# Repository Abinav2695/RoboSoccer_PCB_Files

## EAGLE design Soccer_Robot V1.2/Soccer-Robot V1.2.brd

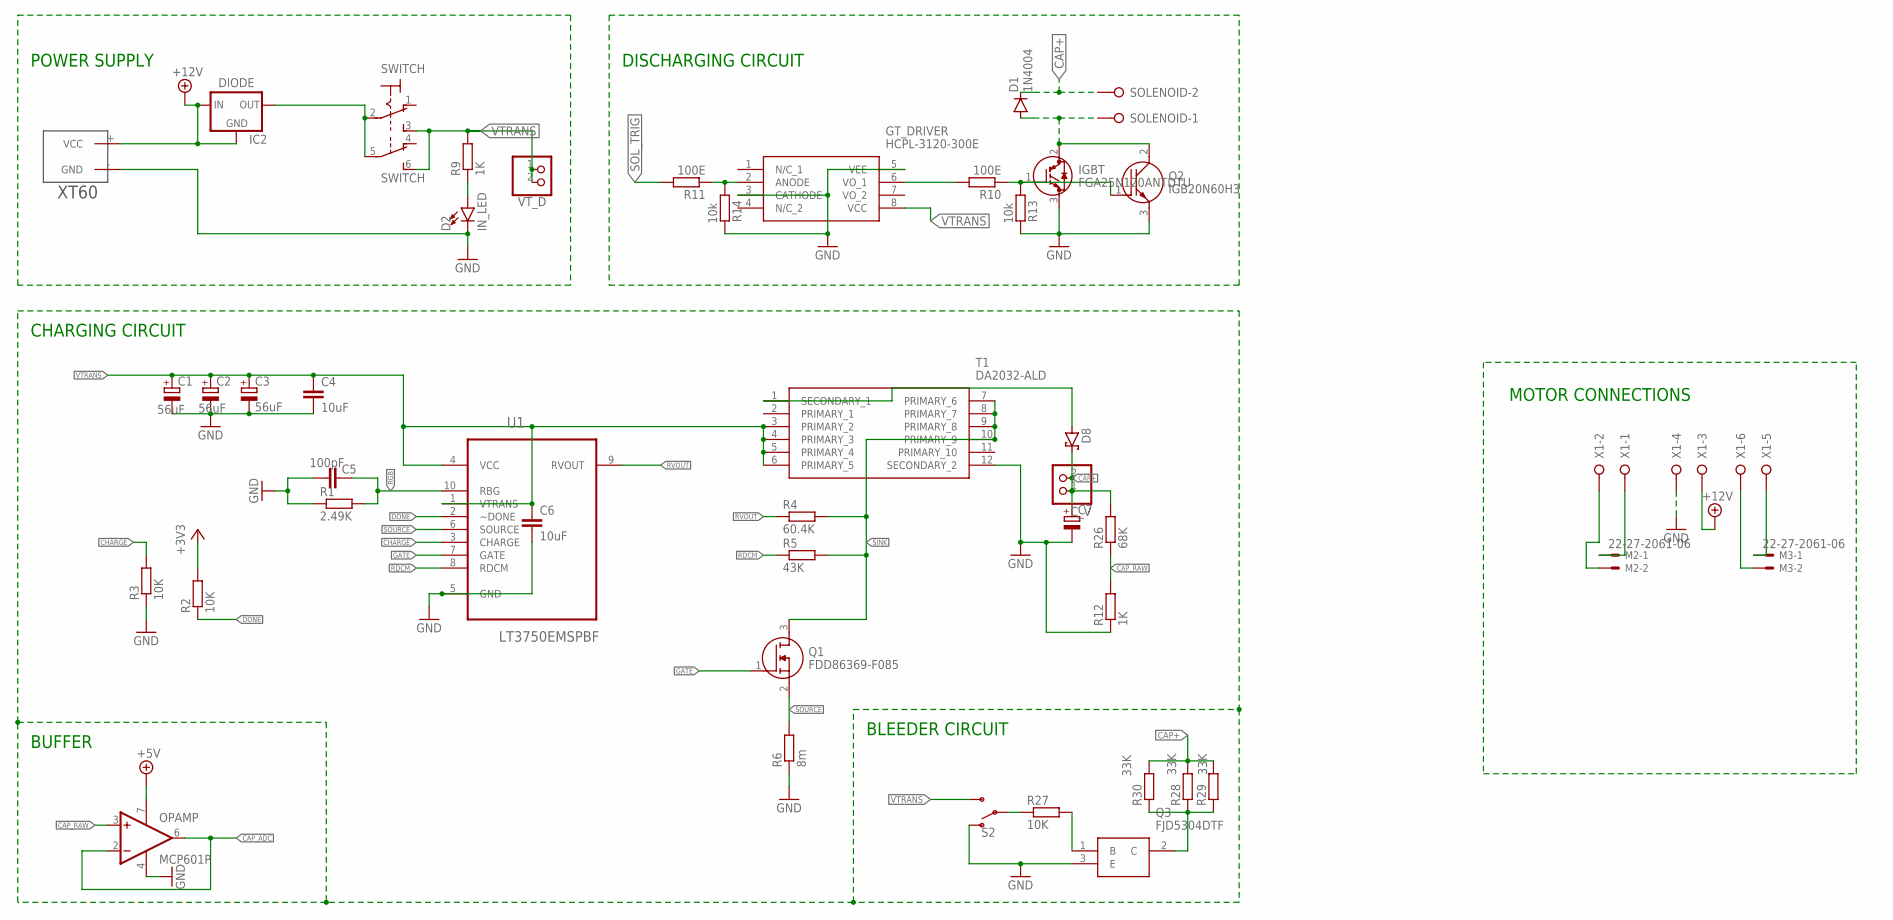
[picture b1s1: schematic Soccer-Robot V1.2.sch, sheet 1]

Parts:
C1, C2, C3: 56uF; E2,5-5
C4, C6: 10uF; C1206
C5: 100pF; C1206
C7: CPOL-EUE10-30; EB30D
C_V: PINHD-1X2; 1X02
D1: 1N4004; DO41-10
D2: IN_LED; LED_5MM
D8: SCHOTTKY-DIODESMC; SMC
GT_DRIVER: HCPL-3120-300E; HCPL-3120-GULL-WING
IC2: DIODE; TO252
IGBT: FGA25N120ANTDTU; TO545P500X1560X2420-3P
M2, M3: 22-27-2061-06; 6410-06
OPAMP: MCP601P; DIL08
Q1: FDD86369-F085; DPAK3-CASE-369AS
Q2: IGB20N60H3; IDB30E60
Q3: FJD5304DTF
R1: 2.49K; M1206
R2, R3, R27: 10K; M1206
R4: 60.4K; M1206
R5: 43K; M1206
R6: 8m; M1206
R9, R12: 1K; M1206
R10, R11: 100E; M1206
R13, R14: 10k; M1206
R26: 68K; M1206
R28, R29, R30: 33K; M1206
S2: SWITCH-SPDT-PTH-11.6X4.0MM; SWITCH_SPDT_PTH_11.6X4.0MM
SOLENOID: W237-02P; W237-132
SWITCH: 320-938
T1: DA2032-ALD; SOP250P2197X889-12N
U1: LT3750EMSPBF; SOP50P490X110-10N
U$1: XT60
VT_D: PINHD-1X2; 1X02
X1: W237-06P; W237-6P

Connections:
+3V3: R2.2; also elsewhere on the board
+5V: OPAMP.7 (V+); also elsewhere on the board
+12V: IC2.1 (GND), IC2.2 (IN), U$1.+ (VCC), X1.3; also elsewhere on the board
CAP+: C7.+, C_V.1, C_V.2, D1.C, D8.C, R26.2, R28.2, R29.2, R30.2, SOLENOID.2
CAP_ADC: OPAMP.2 (-IN), OPAMP.6 (OUT); also elsewhere on the board
CAP_RAW: OPAMP.3 (+IN), R12.2, R26.1
CHARGE: R3.2, U1.3 (CHARGE); also elsewhere on the board
DONE: R2.1, U1.2 (~DONE); also elsewhere on the board
GATE: Q1.1 (G), U1.7 (GATE)
GND: C1.-, C2.-, C3.-, C4.2, C5.2, C6.2, C7.-, D2.K (C), GT_DRIVER.3 (CATHODE), GT_DRIVER.5 (VEE), IGBT.3 (E), OPAMP.4 (V-), Q2.3 (E), Q3.3 (E), R1.1, R3.1, R6.1, R12.1, R13.2, R14.2, S2.1 (O), T1.12 (SECONDARY_2), U1.5 (GND), U$1.- (GND), X1.4; also elsewhere on the board
unnamed: R27.1, S2.2
unnamed: Q3.1 (B), R27.2
unnamed: D8.A, T1.1 (SECONDARY_1)
unnamed: D2.A, R9.1
unnamed: IGBT.1 (G), Q2.1 (G), R10.1, R13.1
unnamed: GT_DRIVER.6 (VO_1), R10.2
unnamed: D1.A, IGBT.2 (C), Q2.2 (C), SOLENOID.1
unnamed: GT_DRIVER.2 (ANODE), R11.1, R14.1
unnamed: M3.1, X1.5
unnamed: M3.2, X1.6
unnamed: M2.2, X1.2
unnamed: M2.1, X1.1
unnamed: Q3.2 (C), R28.1, R29.1, R30.1
RDCM: R5.1, U1.8 (RDCM)
RGB: C5.1, R1.2, U1.10 (RBG)
RVOUT: R4.1, U1.9 (RVOUT)
SINK: Q1.3 (D), R4.2, R5.2, T1.7 (PRIMARY_6), T1.8 (PRIMARY_7), T1.9 (PRIMARY_8), T1.10 (PRIMARY_9)
SOL_TRIG: R11.2; also elsewhere on the board
SOURCE: Q1.2 (S), R6.2, U1.6 (SOURCE)
VIN: IC2.3 (OUT), SWITCH.2, SWITCH.5
VTRANS: C1.+, C2.+, C3.+, C4.1, C6.1, GT_DRIVER.8 (VCC), R9.2, S2.3 (S), SWITCH.3 (S), SWITCH.6 (S), T1.3 (PRIMARY_2), T1.4 (PRIMARY_3), T1.5 (PRIMARY_4), T1.6 (PRIMARY_5), U1.1 (VTRANS), U1.4 (VCC), VT_D.1, VT_D.2

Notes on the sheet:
CHARGING CIRCUIT
BUFFER
POWER SUPPLY
DISCHARGING CIRCUIT
MOTOR CONNECTIONS
BLEEDER CIRCUIT

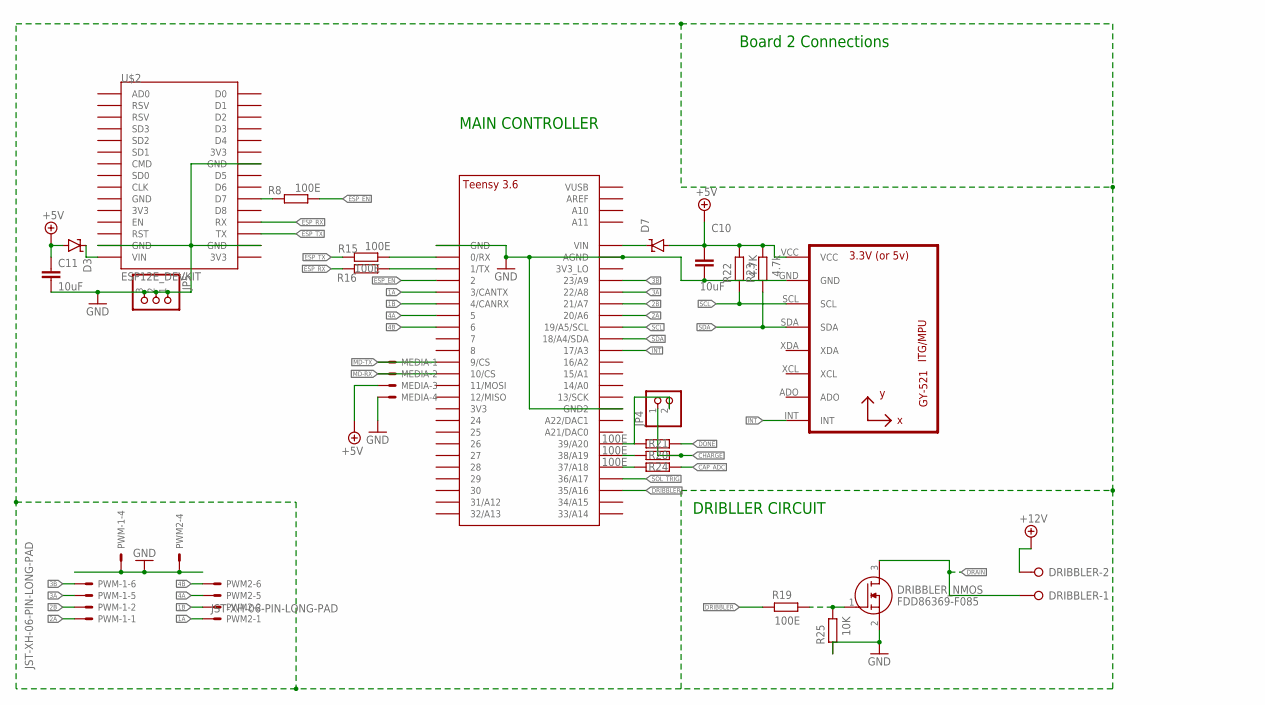
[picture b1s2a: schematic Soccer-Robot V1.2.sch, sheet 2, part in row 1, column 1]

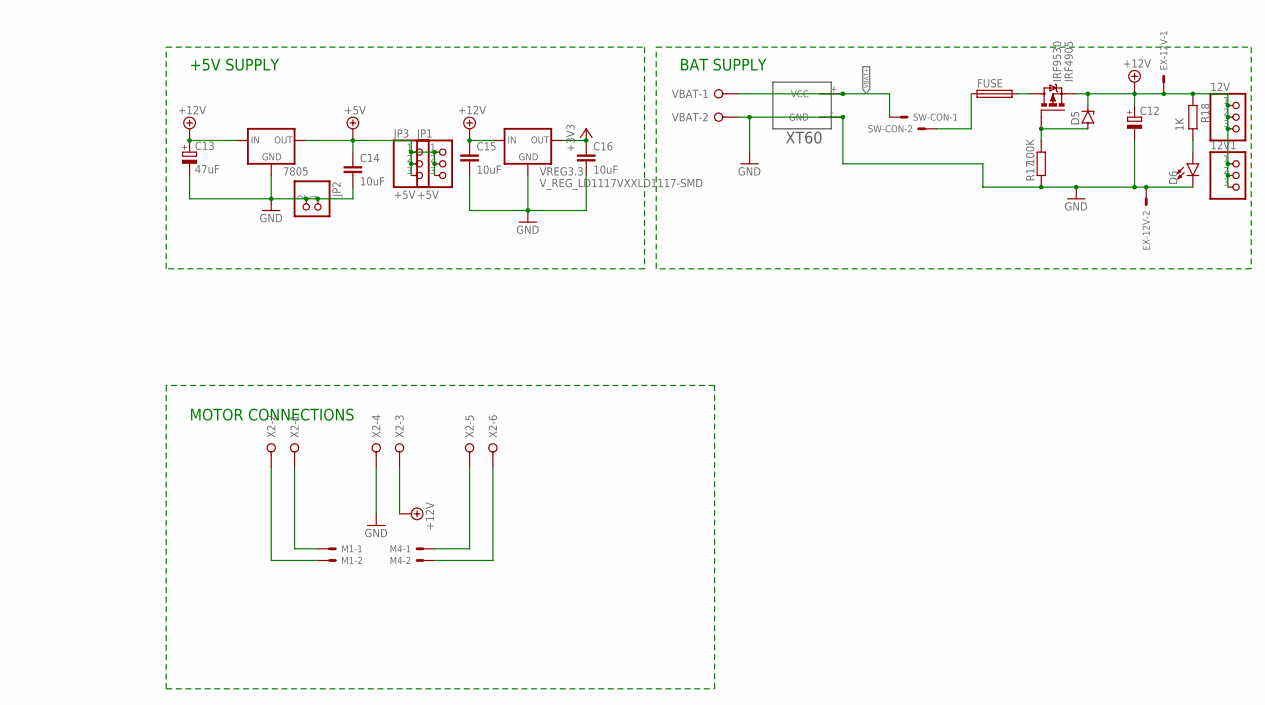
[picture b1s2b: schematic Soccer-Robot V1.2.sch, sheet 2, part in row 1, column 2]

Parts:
12V, 12V1: PINHD-1X3; 1X03
7805: 78XXS
C10, C11, C14, C15, C16: 10uF; C1206
C12: CPOL-EUE2.5-7; E2,5-7
C13: 47uF; E2,5-7
D3, D7: SUPPRESSOR-SMBG; SMBG
D5: ZENER-DIODEDO41Z10; DO41Z10
D6: LED5MM; LED_5MM
DRIBBLER: W237-02P; W237-132
DRIBBLER_NMOS: FDD86369-F085; DPAK3-CASE-369AS
EX-12V: KK-156-2
FUSE: SH22,5A
IRF4905: IRF9530; TO220BV
JP1, JP3: +5V; 1X03
JP2, JP4: PINHD-1X2; 1X02
JP5: PINHD-1X3; 1X03
M1, M4: 22-27-2061-06; 6410-06
MEDIA: JST-XH-04-PIN-LONG-PAD; JST-XH-04-PACKAGE-LONG-PAD
PWM2: JST-XH-06-PIN-LONG-PAD; JST-XH-06-PACKAGE-LONG-PAD
PWM-1: JST-XH-06-PIN-LONG-PAD; JST-XH-06-PACKAGE-LONG-PAD
R8, R15, R16, R19, R20, R21, R24: 100E; M1206
R17: 100K; M1206
R18: 1K; M1206
R22: 4.7K; M1206
R23: 4.7k; M1206
R25: 10K; M1206
SW-CON: KK-156-2
U2: GY-521MPU6050; GY-521
U$2: ESP12E_DEVKIT
U$3: TEENSY_3.5/3.6_BASIC
VBAT: W237-02P; W237-132
VBAT2: XT60
VREG3.3: V_REG_LD1117VXXLD1117-SMD; SOT223
X2: W237-06P; W237-6P

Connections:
1A: PWM2.1, U$3.3/CANTX
1B: PWM2.2, U$3.4/CANRX
2A: PWM-1.1, U$3.20/A6
2B: PWM-1.2, U$3.21/A7
3A: PWM-1.5, U$3.22/A8
3B: PWM-1.6, U$3.23/A9
4A: PWM2.5, U$3.5
4B: PWM2.6, U$3.6
+3V3: C16.1, VREG3.3.2 (OUT), VREG3.3.4 (OUT); also elsewhere on the board
+5V: 7805.OUT, C10.1, C11.1, C14.1, D3.A, D7.A, JP1.1, JP1.2, JP1.3, JP3.1, JP3.2, JP3.3, MEDIA.3, R22.1, R23.1, U2.VCC; also elsewhere on the board
+12V: 12V.1, 12V.2, 12V.3, 12V1.1, 12V1.2, 12V1.3, 7805.IN, C12.+, C13.+, C15.1, D5.C, DRIBBLER.2, EX-12V.1, IRF4905.S, R18.2, VREG3.3.3 (IN), X2.3; also elsewhere on the board
CAP_ADC: R24.2; also elsewhere on the board
CHARGE: JP4.1, R20.2; also elsewhere on the board
DONE: R21.2; also elsewhere on the board
DRAIN: DRIBBLER.1, DRIBBLER_NMOS.3 (D)
DRIBBLER: R19.2, U$3.35/A16
ESP_EN: R8.2, U$3.2
ESP_RX: R16.1, U$2.RX
ESP_TX: R15.1, U$2.TX
GND: 7805.GND, C10.2, C11.2, C12.-, C13.-, C14.2, C15.2, C16.2, D6.K (C), DRIBBLER_NMOS.2 (S), EX-12V.2, JP2.1, JP2.2, JP5.1, JP5.2, JP5.3, MEDIA.4, PWM2.4, PWM-1.4, R17.1, R25.2, U2.GND, U$2.GND@1 (GND), U$2.GND@2 (GND), U$2.GND@3 (GND), U$3.AGND, U$3.GND, U$3.GND2, VBAT.2, VBAT2.- (GND), VREG3.3.1 (GND), X2.4; also elsewhere on the board
INT: U2.INT, U$3.17/A3
MD-RX: MEDIA.2, U$3.10/CS
MD-TX: MEDIA.1, U$3.9/CS
unnamed: R8.1, U$2.D7
unnamed: R15.2, U$3.0/RX
unnamed: R16.2, U$3.1/TX
unnamed: FUSE.2, IRF4905.D
unnamed: D5.A, IRF4905.G, R17.2
unnamed: D6.A, R18.1
unnamed: DRIBBLER_NMOS.1 (G), R19.1, R25.1
unnamed: M4.1, X2.5
unnamed: M4.2, X2.6
unnamed: M1.1, X2.1
unnamed: R20.1, U$3.38/A19
unnamed: JP4.2, R21.1, U$3.39/A20
unnamed: R24.1, U$3.37/A18
unnamed: D3.C, U$2.VIN
unnamed: M1.2, X2.2
unnamed: FUSE.1, SW-CON.2
unnamed: D7.C, U$3.VIN
SCL: R22.2, U2.SCL, U$3.19/A5/SCL
SDA: R23.2, U2.SDA, U$3.18/A4/SDA
SOL_TRIG: U$3.36/A17; also elsewhere on the board
VBAT+: SW-CON.1, VBAT.1, VBAT2.+ (VCC)

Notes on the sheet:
MAIN CONTROLLER
+5V SUPPLY
BAT SUPPLY
MOTOR CONNECTIONS
DRIBLLER CIRCUIT
Board 2 Connections

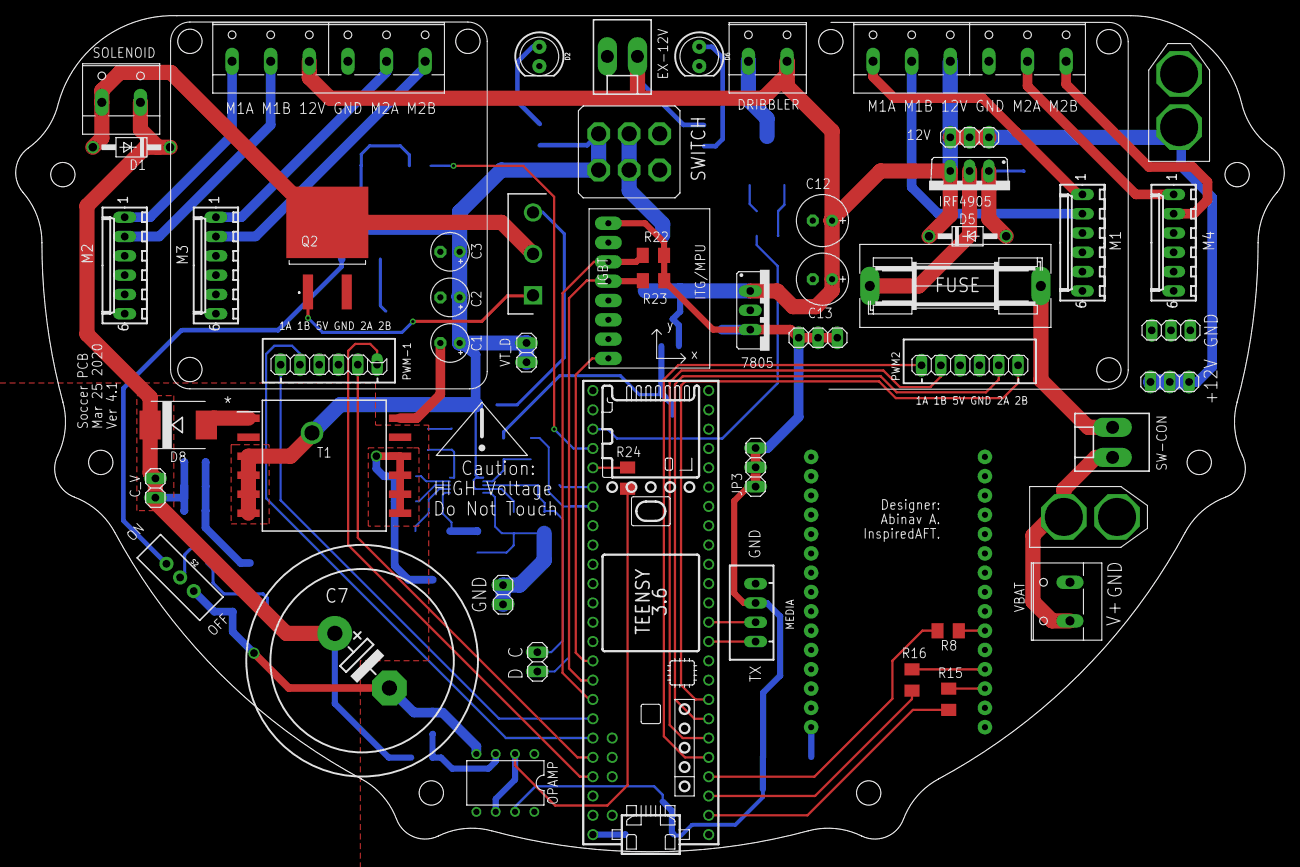
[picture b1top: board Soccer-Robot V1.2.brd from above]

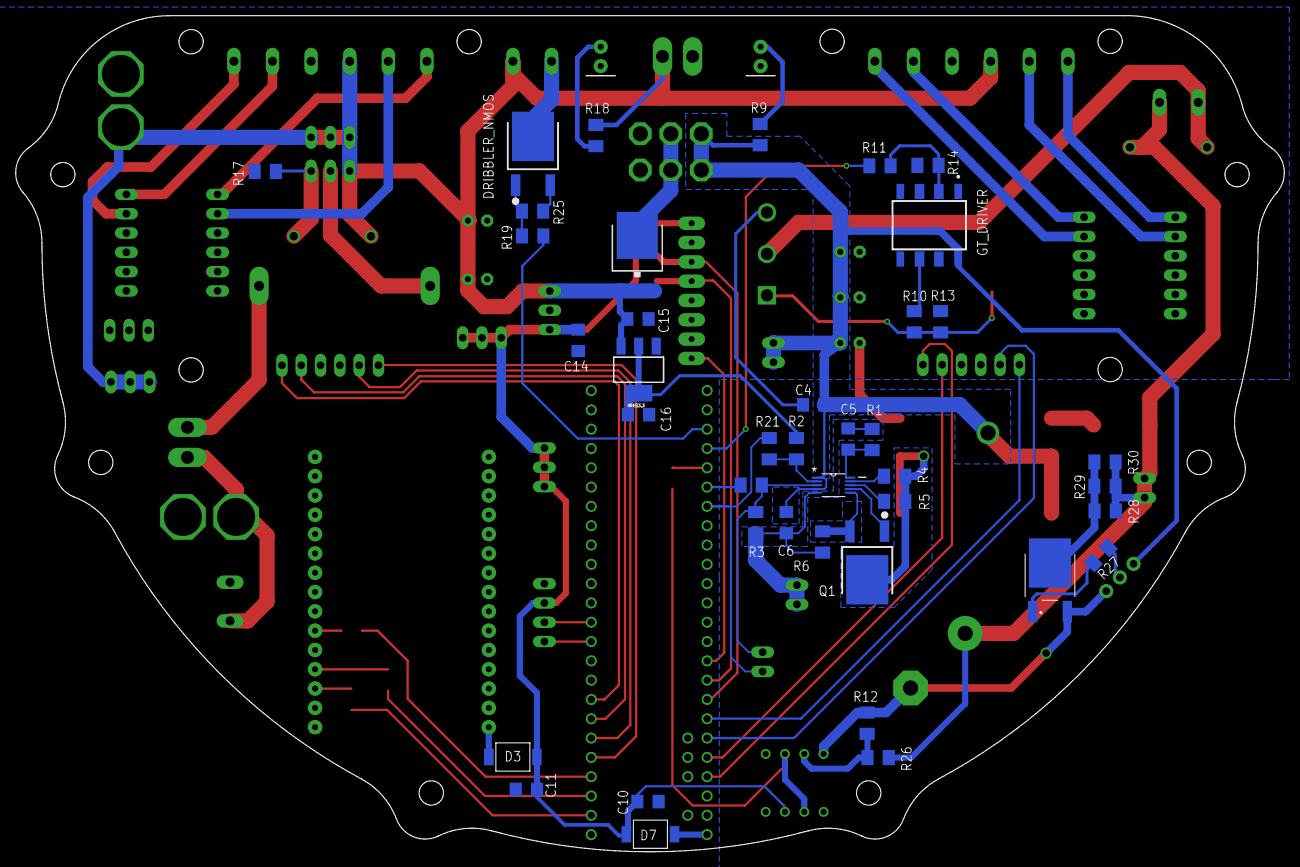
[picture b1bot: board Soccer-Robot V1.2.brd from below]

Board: 2 copper layers, 166.9 x 110.0 mm, 94 parts (40 on the bottom side), 67 nets.

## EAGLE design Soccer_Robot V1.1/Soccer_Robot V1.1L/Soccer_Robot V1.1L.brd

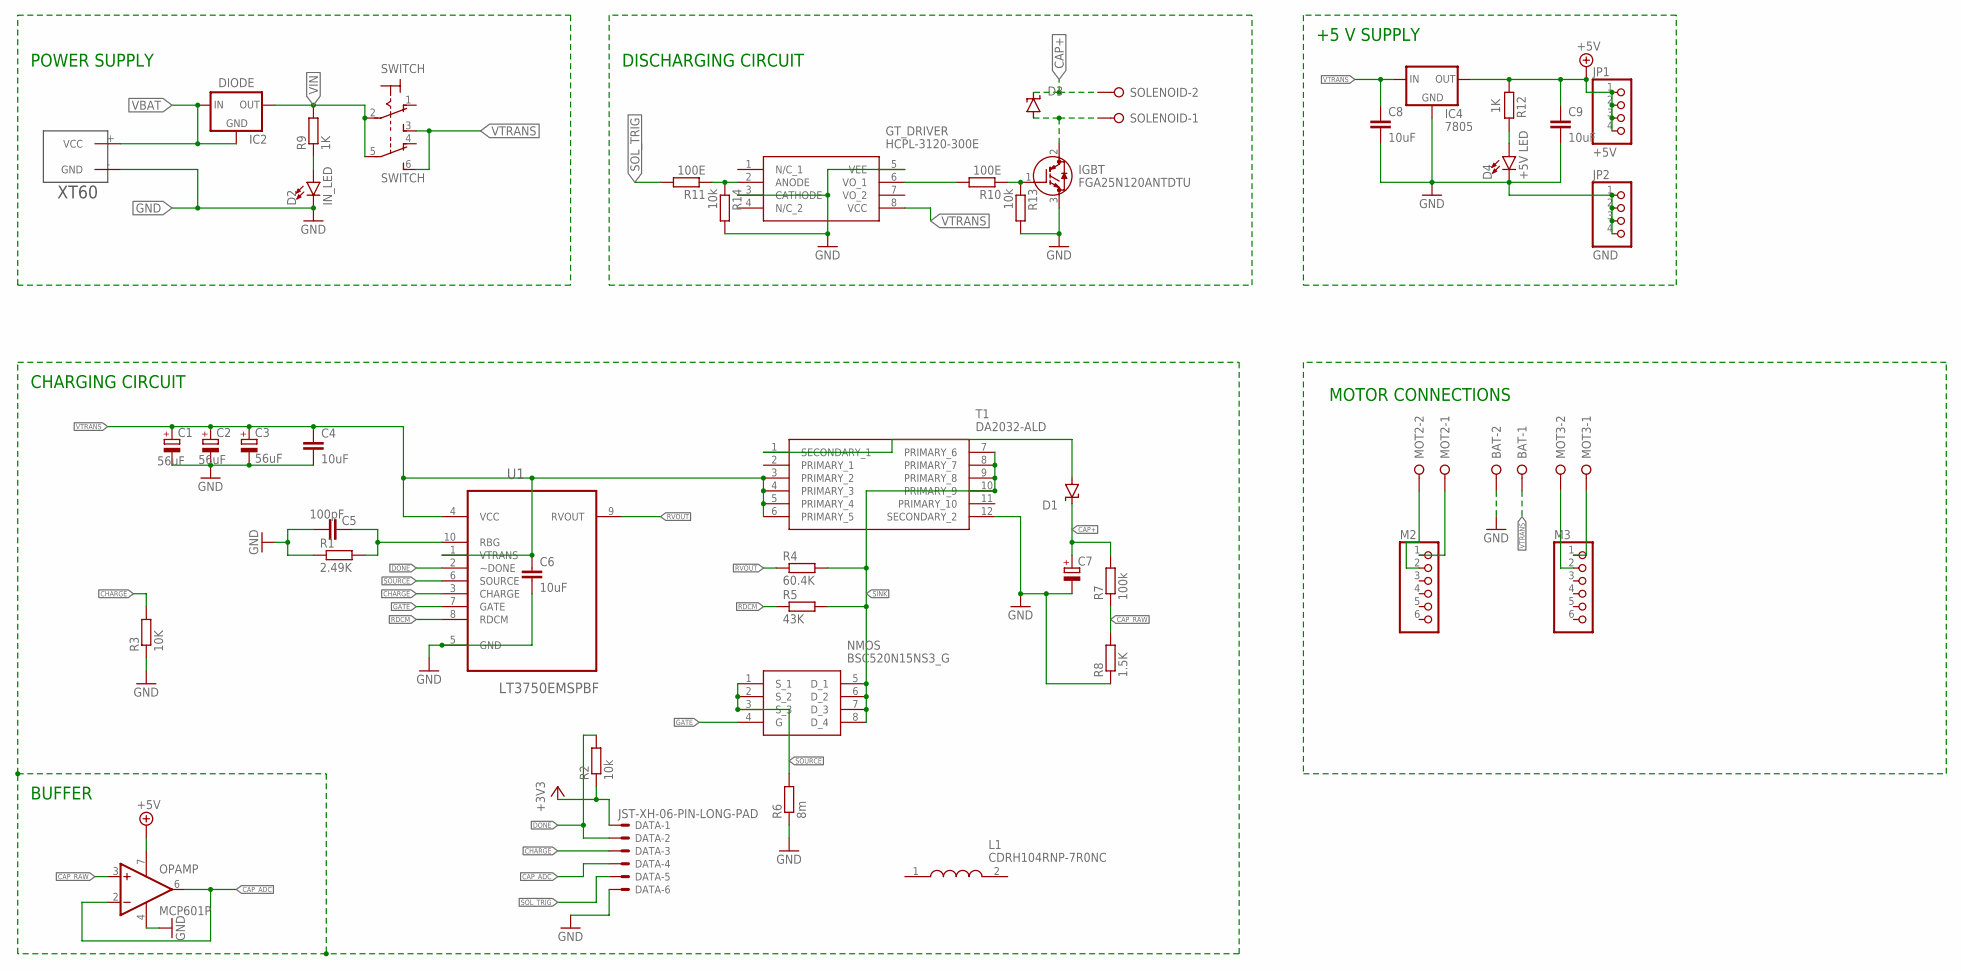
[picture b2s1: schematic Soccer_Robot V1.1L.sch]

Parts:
BAT: W237-02P; W237-132
C1, C2, C3: 56uF; E2,5-5
C4, C6, C8, C9: 10uF; C1206
C5: 100pF; C1206
C7: CPOL-EUE10-30; EB30D
D1, D3: SUPPRESSOR-SMBG; SMBG
D2: IN_LED; LED_5MM
D4: +5V LED; LED_5MM
DATA: JST-XH-06-PIN-LONG-PAD; JST-XH-06-PACKAGE-LONG-PAD
GT_DRIVER: HCPL-3120-300E; HCPL-3120-GULL-WING
IC2: DIODE; TO252
IC4: 7805; 78XXS
IGBT: FGA25N120ANTDTU; TO545P500X1560X2420-3P
JP1: +5V; 1X04
JP2: GND; 1X04
L1: CDRH104RNP-7R0NC; CDRH104RNP7R0NC
M2, M3: PINHD-1X6; 1X06
MOT2, MOT3: W237-02P; W237-132
NMOS: BSC520N15NS3_G; PG-TDSON-8
OPAMP: MCP601P; DIL08
R1: 2.49K; M1206
R2, R13, R14: 10k; M1206
R3: 10K; M1206
R4: 60.4K; M1206
R5: 43K; M1206
R6: 8m; M1206
R7: 100k; 0207/10
R8: 1.5K; 0207/10
R9, R12: 1K; M1206
R10, R11: 100E; M1206
SOLENOID: W237-02P; W237-132
SWITCH: 320-938
T1: DA2032-ALD; SOP250P2197X889-12N
U1: LT3750EMSPBF; SOP50P490X110-10N
U$1: XT60

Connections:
+3V3: DATA.1, R2.1
+5V: C9.1, IC4.OUT, JP1.1, JP1.2, JP1.3, JP1.4, OPAMP.7 (V+), R12.1
CAP+: C7.+, D1.C, D3.C, R7.2, SOLENOID.2
CAP_ADC: DATA.4, OPAMP.2 (-IN), OPAMP.6 (OUT)
CAP_RAW: OPAMP.3 (+IN), R7.1, R8.2
CHARGE: DATA.3, R3.2, U1.3 (CHARGE)
DONE: DATA.2, R2.2, U1.2 (~DONE)
GATE: NMOS.4 (G), U1.7 (GATE)
GND: BAT.2, C1.-, C2.-, C3.-, C4.2, C5.2, C6.2, C7.-, C8.2, C9.2, D2.K (C), D4.K (C), DATA.6, GT_DRIVER.3 (CATHODE), GT_DRIVER.5 (VEE), IC4.GND, IGBT.3 (E), JP2.1, JP2.2, JP2.3, JP2.4, OPAMP.4 (V-), R1.1, R3.1, R6.1, R8.1, R13.2, R14.2, T1.12 (SECONDARY_2), U1.5 (GND), U$1.- (GND)
unnamed: C5.1, R1.2, U1.10 (RBG)
unnamed: D1.A, T1.1 (SECONDARY_1)
unnamed: D2.A, R9.1
unnamed: IGBT.1 (G), R10.1, R13.1
unnamed: GT_DRIVER.6 (VO_1), R10.2
unnamed: D3.A, IGBT.2 (C), SOLENOID.1
unnamed: GT_DRIVER.2 (ANODE), R11.1, R14.1
unnamed: M3.1, MOT3.1
unnamed: D4.A, R12.2
unnamed: M3.2, MOT3.2
unnamed: M2.2, MOT2.2
unnamed: M2.1, MOT2.1
RDCM: R5.1, U1.8 (RDCM)
RVOUT: R4.1, U1.9 (RVOUT)
SINK: NMOS.5 (D_1), NMOS.6 (D_2), NMOS.7 (D_3), NMOS.8 (D_4), R4.2, R5.2, T1.7 (PRIMARY_6), T1.8 (PRIMARY_7), T1.9 (PRIMARY_8), T1.10 (PRIMARY_9)
SOL_TRIG: DATA.5, R11.2
SOURCE: NMOS.1 (S_1), NMOS.2 (S_2), NMOS.3 (S_3), R6.2, U1.6 (SOURCE)
VBAT: IC2.1 (GND), IC2.2 (IN), U$1.+ (VCC)
VIN: IC2.3 (OUT), R9.2, SWITCH.2, SWITCH.5
VTRANS: BAT.1, C1.+, C2.+, C3.+, C4.1, C6.1, C8.1, GT_DRIVER.8 (VCC), IC4.IN, SWITCH.3 (S), SWITCH.6 (S), T1.3 (PRIMARY_2), T1.4 (PRIMARY_3), T1.5 (PRIMARY_4), T1.6 (PRIMARY_5), U1.1 (VTRANS), U1.4 (VCC)

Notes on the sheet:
CHARGING CIRCUIT
BUFFER
POWER SUPPLY
DISCHARGING CIRCUIT
+5 V SUPPLY
MOTOR CONNECTIONS

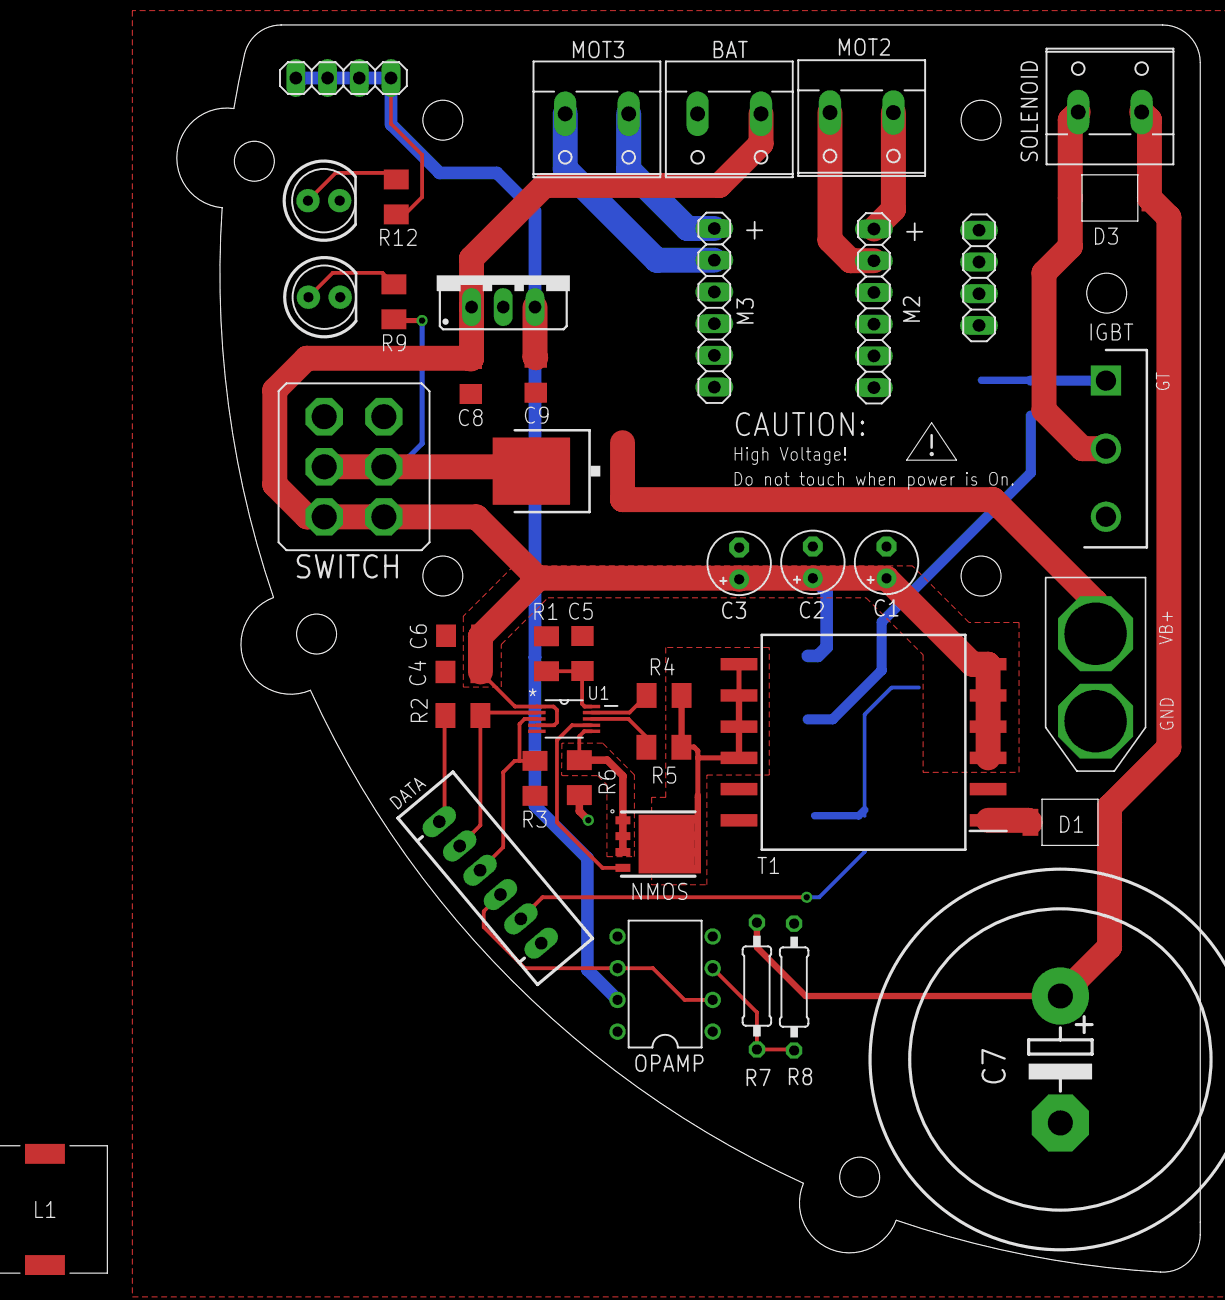
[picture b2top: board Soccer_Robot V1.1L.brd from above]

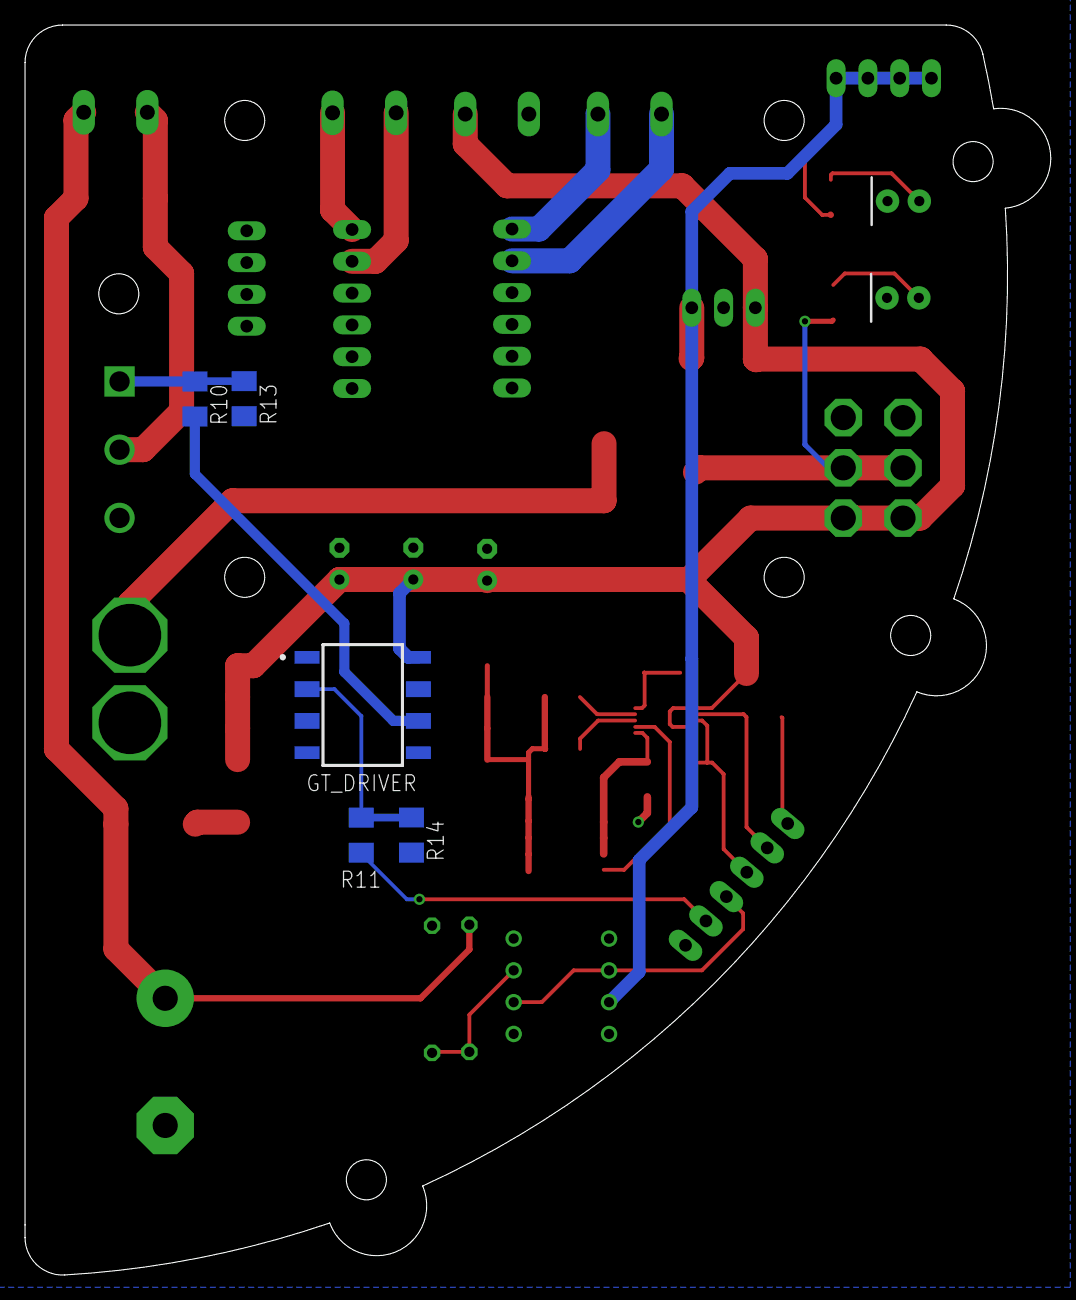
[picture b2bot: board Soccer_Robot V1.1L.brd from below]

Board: 2 copper layers, 82.0 x 99.9 mm, 47 parts (5 on the bottom side), 29 nets.

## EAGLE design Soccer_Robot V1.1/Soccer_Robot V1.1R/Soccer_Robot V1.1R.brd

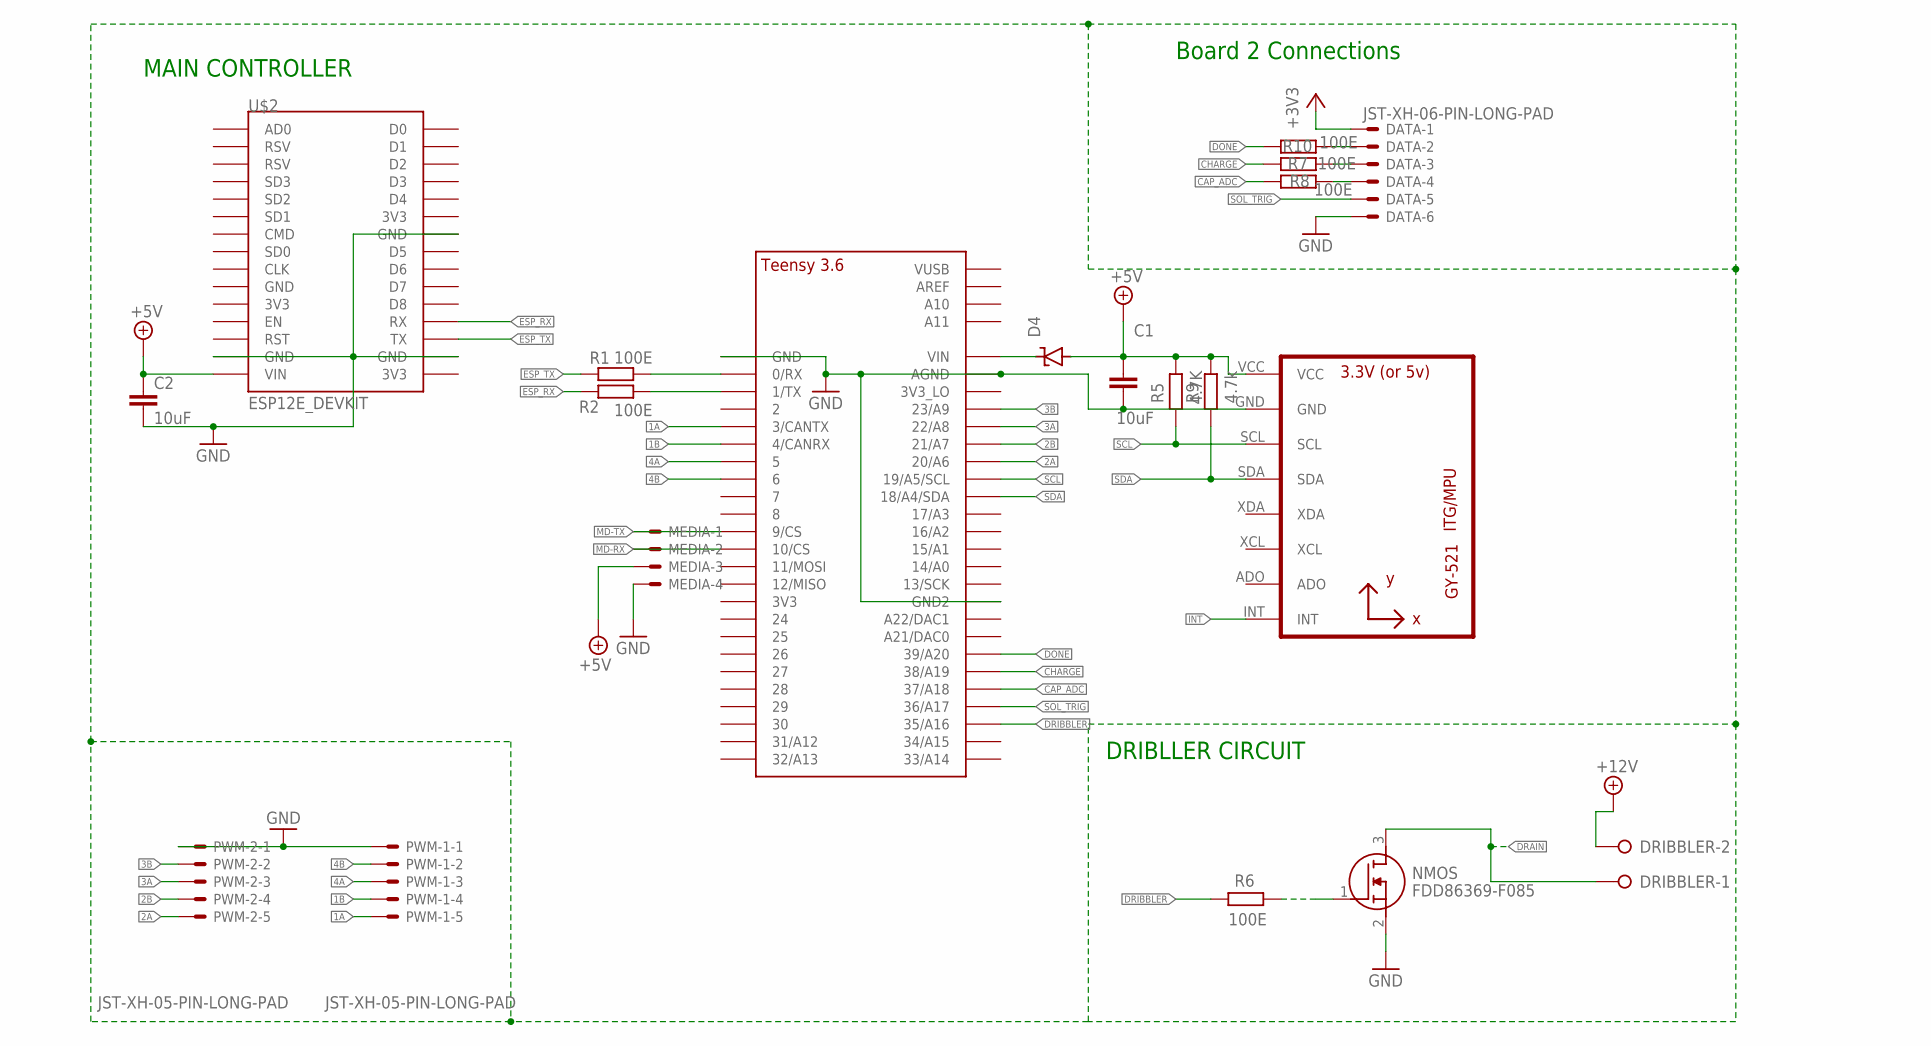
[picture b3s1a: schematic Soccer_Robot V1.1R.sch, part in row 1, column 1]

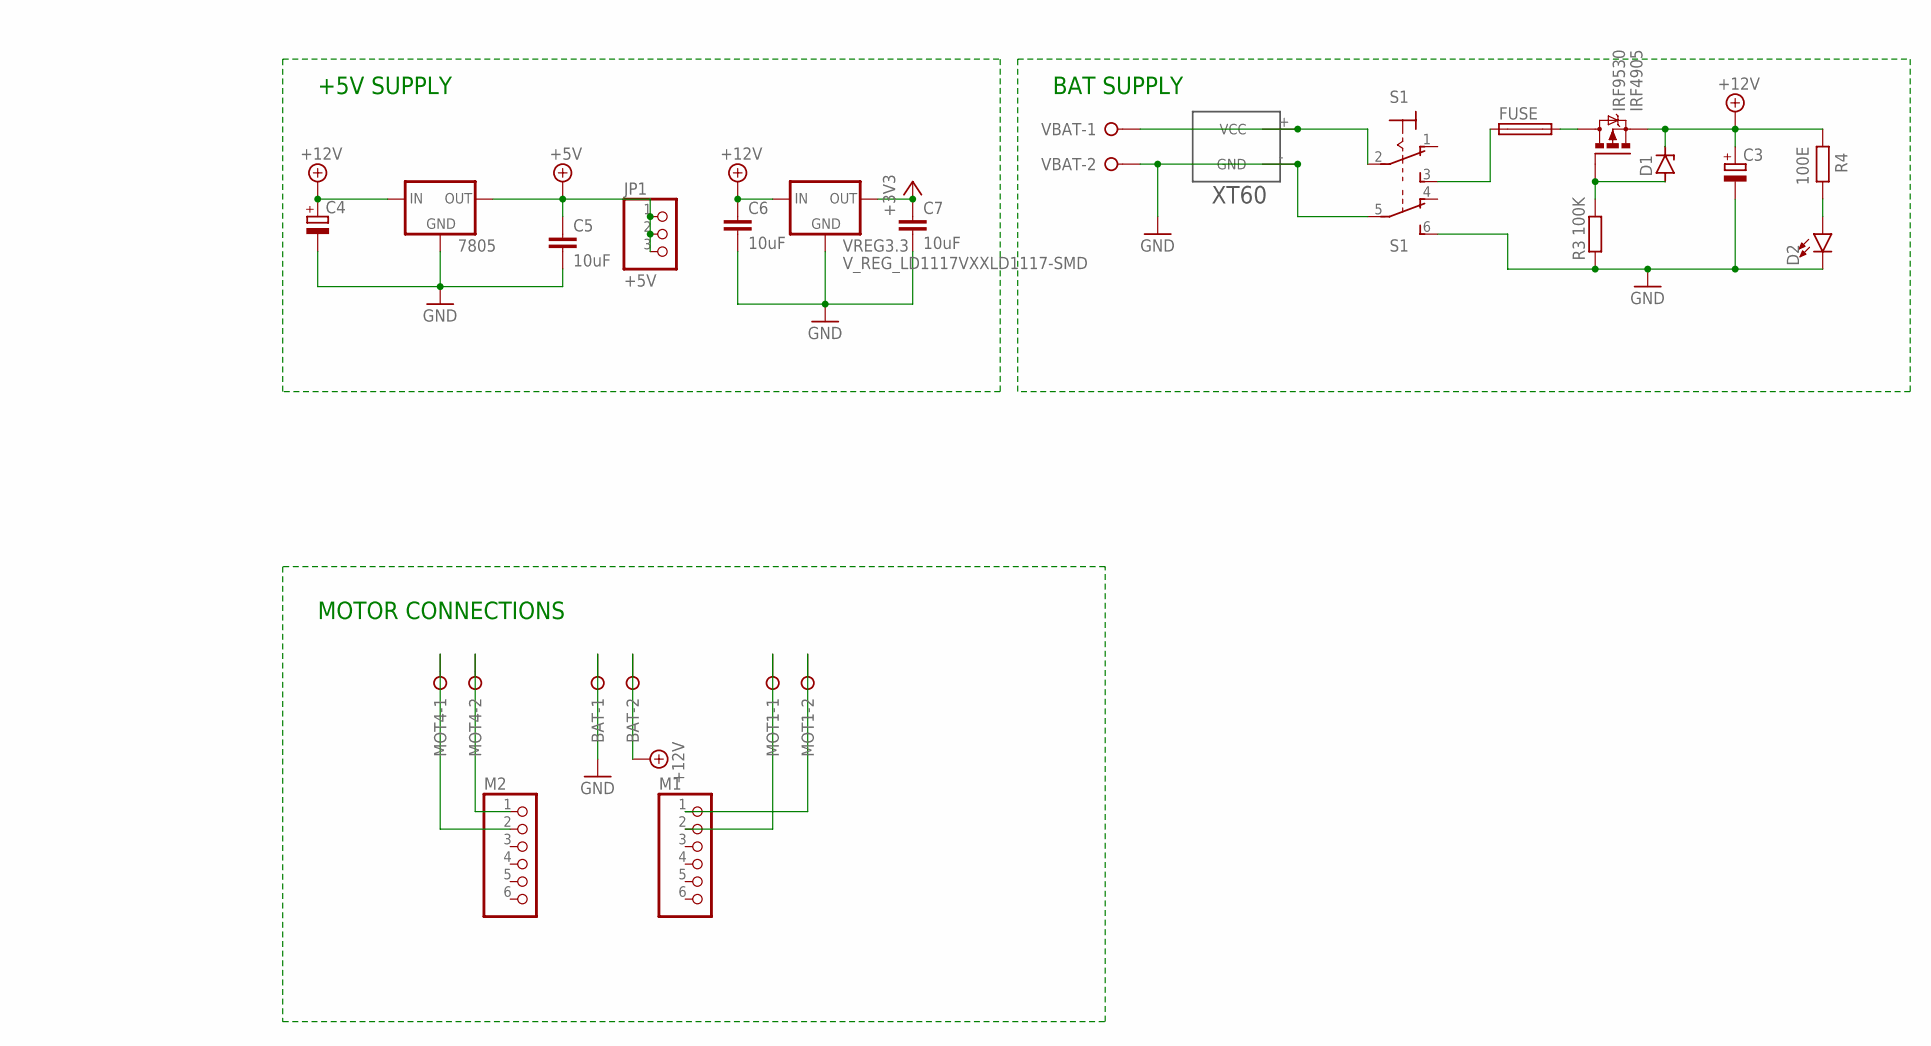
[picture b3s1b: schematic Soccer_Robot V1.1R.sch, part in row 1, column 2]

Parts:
7805: 78XXS
BAT: W237-02P; W237-132
C1, C2, C5, C6, C7: 10uF; C1206
C3, C4: CPOL-EUE2.5-7; E2,5-7
D1: ZENER-DIODEDO41Z10; DO41Z10
D2: LED5MM; LED_5MM
D4: SUPPRESSOR-SMBG; SMBG
DATA: JST-XH-06-PIN-LONG-PAD; JST-XH-06-PACKAGE-LONG-PAD
DRIBBLER: W237-02P; W237-132
FUSE: SH22,5A
IRF4905: IRF9530; TO220BV
JP1: +5V; 1X03
M1, M2: PINHD-1X6; 1X06
MEDIA: JST-XH-04-PIN-LONG-PAD; JST-XH-04-PACKAGE-LONG-PAD
MOT1, MOT4: W237-02P; W237-132
NMOS: FDD86369-F085; DPAK3-CASE-369AS
PWM-1, PWM-2: JST-XH-05-PIN-LONG-PAD; JST-XH-05-PACKAGE-LONG-PAD
R1, R2, R4, R6, R7, R8, R10: 100E; M1206
R3: 100K; M1206
R5: 4.7K; M1206
R9: 4.7k; M1206
S1: 320-938
U1: GY-521MPU6050; GY-521
U$1: TEENSY_3.5/3.6_BASIC
U$2: ESP12E_DEVKIT
VBAT: W237-02P; W237-132
VBAT2: XT60
VREG3.3: V_REG_LD1117VXXLD1117-SMD; SOT223

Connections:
1A: PWM-1.5, U$1.3/CANTX
1B: PWM-1.4, U$1.4/CANRX
2A: PWM-2.5, U$1.20/A6
2B: PWM-2.4, U$1.21/A7
3A: PWM-2.3, U$1.22/A8
3B: PWM-2.2, U$1.23/A9
4A: PWM-1.3, U$1.5
4B: PWM-1.2, U$1.6
+3V3: C7.1, DATA.1, VREG3.3.2 (OUT), VREG3.3.4 (OUT)
+5V: 7805.OUT, C1.1, C2.1, C5.1, D4.A, JP1.1, JP1.2, JP1.3, MEDIA.3, R5.1, R9.1, U1.VCC, U$2.VIN
+12V: 7805.IN, BAT.2, C3.+, C4.+, C6.1, D1.C, DRIBBLER.2, IRF4905.S, R4.2, VREG3.3.3 (IN)
CAP_ADC: R8.1, U$1.37/A18
CHARGE: R7.1, U$1.38/A19
DONE: R10.1, U$1.39/A20
DRAIN: DRIBBLER.1, NMOS.3 (D)
DRIBBLER: R6.2, U$1.35/A16
ESP_RX: R2.1, U$2.RX
ESP_TX: R1.1, U$2.TX
GND: 7805.GND, BAT.1, C1.2, C2.2, C3.-, C4.-, C5.2, C6.2, C7.2, D2.K (C), DATA.6, MEDIA.4, NMOS.2 (S), PWM-1.1, PWM-2.1, R3.1, S1.5, S1.6 (S), U1.GND, U$1.AGND, U$1.GND, U$1.GND2, U$2.GND@1 (GND), U$2.GND@2 (GND), U$2.GND@3 (GND), VBAT.2, VBAT2.- (GND), VREG3.3.1 (GND)
INT: U1.INT
MD-RX: MEDIA.2, U$1.10/CS
MD-TX: MEDIA.1, U$1.9/CS
unnamed: R1.2, U$1.0/RX
unnamed: R2.2, U$1.1/TX
unnamed: DATA.2, R10.2
unnamed: S1.2, VBAT.1, VBAT2.+ (VCC)
unnamed: FUSE.2, IRF4905.D
unnamed: NMOS.1 (G), R6.1
unnamed: D1.A, IRF4905.G, R3.2
unnamed: D2.A, R4.1
unnamed: M1.1, MOT1.2
unnamed: M1.2, MOT1.1
unnamed: M2.1, MOT4.2
unnamed: M2.2, MOT4.1
unnamed: FUSE.1, S1.3 (S)
unnamed: DATA.3, R7.2
unnamed: DATA.4, R8.2
unnamed: D4.C, U$1.VIN
SCL: R5.2, U1.SCL, U$1.19/A5/SCL
SDA: R9.2, U1.SDA, U$1.18/A4/SDA
SOL_TRIG: DATA.5, U$1.36/A17

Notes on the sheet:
MAIN CONTROLLER
+5V SUPPLY
BAT SUPPLY
MOTOR CONNECTIONS
DRIBLLER CIRCUIT
Board 2 Connections

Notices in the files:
parts and their libraries:
SparkFun-LED: Licensing: Creative Commons ShareAlike 4.0 International - https://creativecommons.org/licenses/by-sa/4.0
SparkFun: Licensing: CC v3.0 Share-Alike You are welcome to use this library for commercial purposes.
